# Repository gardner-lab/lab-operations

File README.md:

# lab-operations
Code and information that is useful for day-to-day lab operations.

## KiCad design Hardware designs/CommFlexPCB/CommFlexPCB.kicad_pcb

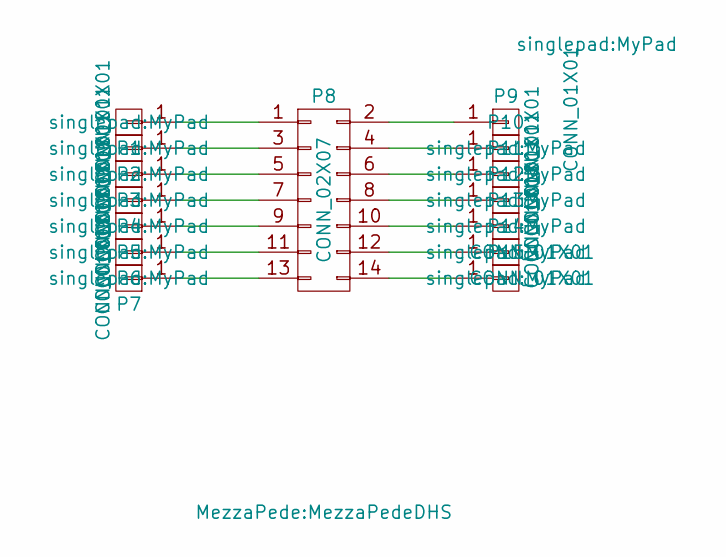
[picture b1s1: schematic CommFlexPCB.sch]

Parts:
P1, P2, P3, P4, P5, P6, P7, P9, P10, P11, P12, P13, P14, P15: CONN_01X01; MyPad
P8: CONN_02X07; MezzaPedeDHS

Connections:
unnamed: P1.1, P8.1
unnamed: P2.1, P8.3
unnamed: P3.1, P8.5
unnamed: P4.1, P8.7
unnamed: P5.1, P8.9
unnamed: P6.1, P8.11
unnamed: P7.1, P8.13
unnamed: P8.2, P9.1
unnamed: P8.4, P10.1
unnamed: P8.6, P11.1
unnamed: P8.8, P12.1
unnamed: P8.10, P13.1
unnamed: P8.12, P14.1
unnamed: P8.14, P15.1

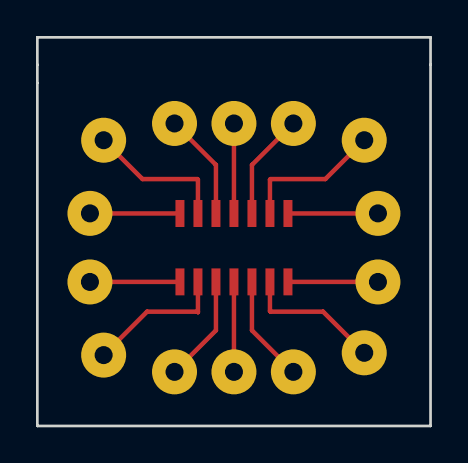
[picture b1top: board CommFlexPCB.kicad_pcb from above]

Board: 2 copper layers, 21.8 x 21.6 mm, 15 parts (0 on the bottom side), 14 nets.

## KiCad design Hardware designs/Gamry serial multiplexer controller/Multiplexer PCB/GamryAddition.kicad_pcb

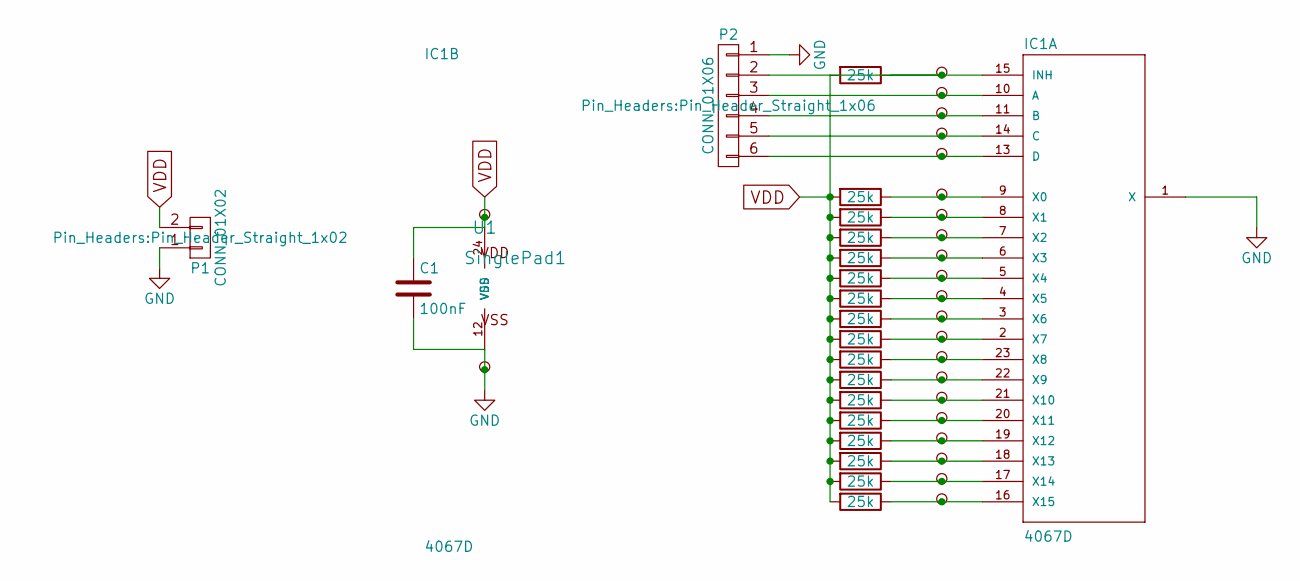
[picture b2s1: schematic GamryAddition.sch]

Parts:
C1: 100nF; C_0603_HandSoldering
IC1: 4067D; 40xx-SO24W
P1: CONN_01X02; Pin_Header_Straight_1x02
P2: CONN_01X06; Pin_Header_Straight_1x06
R1, R2, R3, R4, R5, R6, R7, R8, R9, R10, R11, R12, R13, R14, R15, R16, R17: 25k; R_0603_HandSoldering
U1, U2, U3, U4, U5, U6, U7, U8, U9, U10, U11, U12, U13, U14, U15, U16, U17, U18, U19, U20, U21, U22, U23: SinglePad1; hole1

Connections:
GND: C1.2, IC1.1 (X), IC1.12 (VSS), P1.1, P2.1, U2.?
unnamed: IC1.2 (X7), R9.1, U15.?
unnamed: IC1.3 (X6), R8.1, U14.?
unnamed: IC1.4 (X5), R7.1, U13.?
unnamed: IC1.5 (X4), R6.1, U12.?
unnamed: IC1.6 (X3), R5.1, U11.?
unnamed: IC1.7 (X2), R4.1, U10.?
unnamed: IC1.8 (X1), R3.1, U9.?
unnamed: IC1.9 (X0), R2.1, U8.?
unnamed: IC1.10 (A), P2.3, U4.?
unnamed: IC1.11 (B), P2.4, U5.?
unnamed: IC1.13 (D), P2.6, U7.?
unnamed: IC1.14 (C), P2.5, U6.?
unnamed: IC1.15 (INH), P2.2, R1.1, U3.?
unnamed: IC1.16 (X15), R17.1, U23.?
unnamed: IC1.17 (X14), R16.1, U22.?
unnamed: IC1.18 (X13), R15.1, U21.?
unnamed: IC1.19 (X12), R14.1, U20.?
unnamed: IC1.20 (X11), R13.1, U19.?
unnamed: IC1.21 (X10), R12.1, U18.?
unnamed: IC1.22 (X9), R11.1, U17.?
unnamed: IC1.23 (X8), R10.1, U16.?
VDD: C1.1, IC1.24 (VDD), P1.2, R1.2, R2.2, R3.2, R4.2, R5.2, R6.2, R7.2, R8.2, R9.2, R10.2, R11.2, R12.2, R13.2, R14.2, R15.2, R16.2, R17.2, U1.?

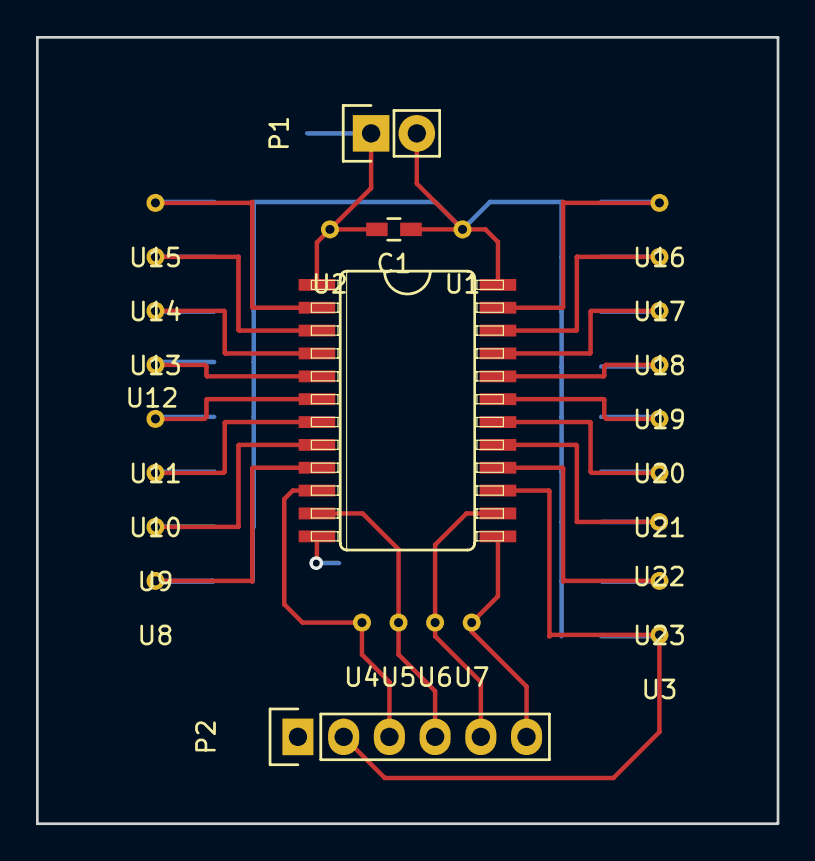
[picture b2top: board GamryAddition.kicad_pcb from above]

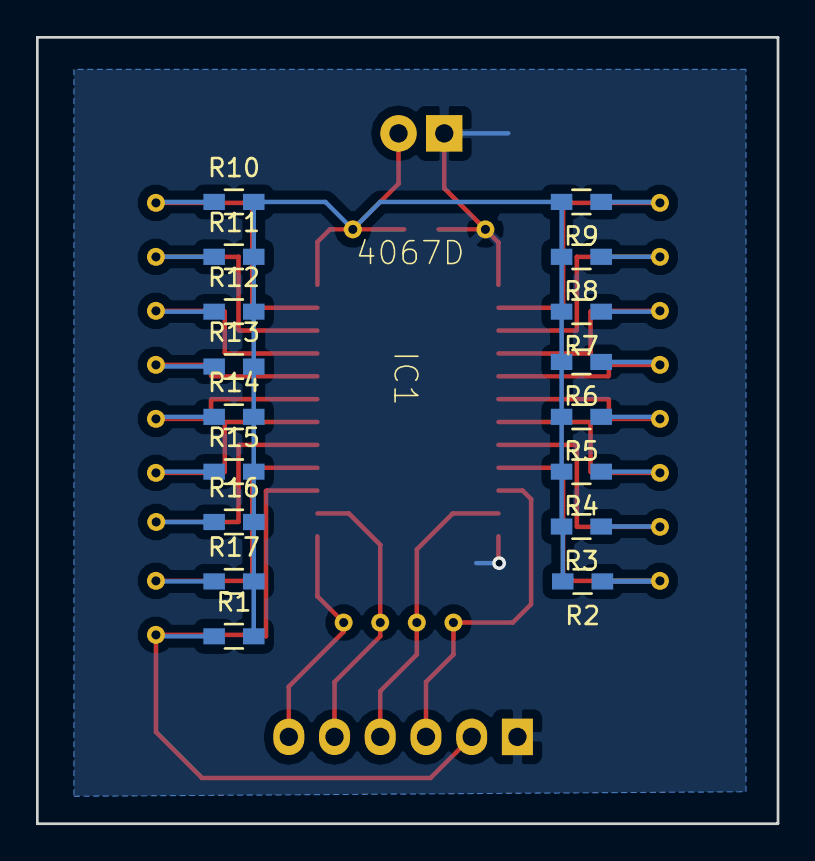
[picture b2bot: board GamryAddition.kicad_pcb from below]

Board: 2 copper layers, 41.1 x 43.7 mm, 44 parts (17 on the bottom side), 23 nets.

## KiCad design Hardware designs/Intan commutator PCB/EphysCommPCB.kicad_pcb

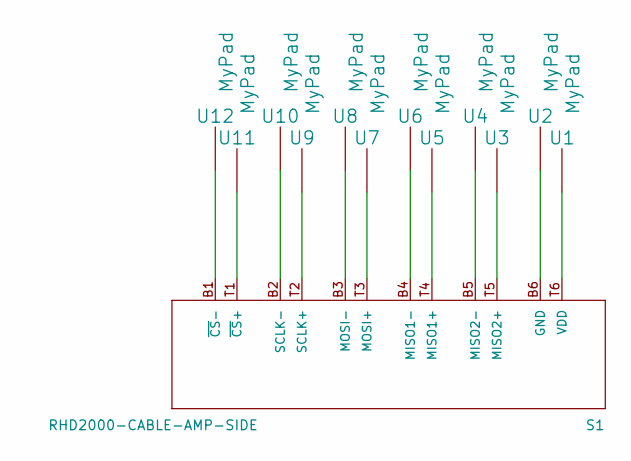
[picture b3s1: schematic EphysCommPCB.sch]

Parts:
S1: RHD2000-CABLE-AMP-SIDE; OMNETICS_PZN-12-AA
U1, U2, U3, U4, U5, U6, U7, U8, U9, U10, U11, U12: MyPad

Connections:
unnamed: S1.B1 (~CS~-), U12.1
unnamed: S1.B2 (SCLK-), U10.1
unnamed: S1.B3 (MOSI-), U8.1
unnamed: S1.B4 (MISO1-), U6.1
unnamed: S1.B5 (MISO2-), U4.1
unnamed: S1.B6 (GND), U2.1
unnamed: S1.T1 (~CS~+), U11.1
unnamed: S1.T2 (SCLK+), U9.1
unnamed: S1.T3 (MOSI+), U7.1
unnamed: S1.T4 (MISO1+), U5.1
unnamed: S1.T5 (MISO2+), U3.1
unnamed: S1.T6 (VDD), U1.1

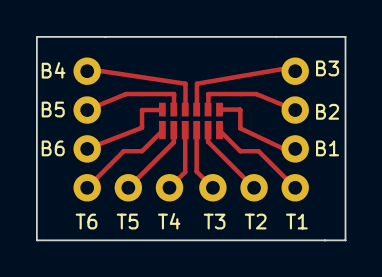
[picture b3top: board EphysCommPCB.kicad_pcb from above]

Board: 2 copper layers, 17.1 x 11.3 mm, 13 parts (0 on the bottom side), 12 nets.

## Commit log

2016-05-04 Short script for reading Gamry .DTA files (MATLAB)
2016-05-06 Short script for reading nanoZ files
2016-05-19 Reorganize utilities
2016-05-19 Add images
2016-05-26 Move images and add screenshots
2016-05-26 very small scripts
2016-05-26 moved
2016-07-26 Flex cable pub for intan.
    KiCad sources and gerber files
2016-07-26 Intan digital cable breakout board
2016-07-26 Electronics for performing serial operations in Gamry
2016-09-09 Basic system for sensor monitoring
2016-10-19 mov converter
2016-10-20 reordering
2017-01-13 Post-op cards
2017-01-13 add email notifications
2017-01-13 simple audio summary
2017-01-13 bulk
2017-01-23 Add logger options
    For all analog inputs in an arduino Mega 2560
2017-12-09 Deleted deprecated code
2019-02-05 Commutator pcb for finchscope
